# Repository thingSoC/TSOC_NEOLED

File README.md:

# TSOC_NEOLED

**TSOC_NEOLED** is a Eight-Channel WS2812 LED driver expansion board, and can drive
eight (8) to sixteen(16) strips of individually addressable Light Emitting Diodes (LEDs). 

**TSOC_NEOLED** uses a programmable system on chip (PSoC4) with an eight (8) channel driver
to drive hundreds of WS2812 Color LED's, with a default arrangement of 8 (eight strings) of sixty-four(64) LEDs each.

The **TSOC_NEOLED** can provide several different intefaces in order to make
interfacing large numbers of LEDs easy. The default protocol is an I2C interface :

1) I2C Serial DMX-512, Memory Mapped (**TSOC_NEOLED** looks like a 2048 byte I2C SRAM)

Other Interface protocols are possible (Firmware update using FTDI/USB-UART or JTAG) :

- UART Serial DMX-512 (200K Baud, N, 8, 1) with four DMX universes.

- SPI Serial DMX-512, Memory Mapped (**TSOC_NEOLED** looks like a 2048 byte SPI SRAM)

[TSOC_NEOLED](https://github.com/thingSoC/TSOC_NEOLED)

**thingSoC Reference Designs** are example thingSoC implementations that implement
various reference and testing circuits for demonstrating the use of the thingSoC libraries.
These reference designs can serve as starting templates for user designs.

---------------------------------------

## TSOC_NEOLED Application Pictures

Using the TSOC_NEOLED to drive eight(8) strings of color LEDs for lighting our tandem bike for Portland PedalPolooza 2016

[*TSOC_NEOLED*](https://github.com/thingSoC/TSOC_NEOLED)

---------------------------------------

## TSOC_NEOLED Arduino Sketch Examples

Under the "examples" directory are several Arduino IDE examples for using the TSOC_NEOLED board with Arduino IDE.
Using the Arduino "Wire" library for I2C communications, it is simple to control the TSOC_NEOLED

```c
  // Start the Arduino I2C Interface
  wire.begin();

  // Turn the first LED On (i.e. green LED #1) 
  // the LED's are (GRBY) color order in memory
  byte row, column = 0;
  Wire.beginTransmission(TSOC_NEOLED_I2CADDRESS);  // Start the I2C transaction
  Wire.write(row);                                 // Send the high byte of 16 bit memory address
  Wire.write(column);                              // Send the low byte of 16 bit memory address
  Wire.write(TSOC_NEOLED_LED_ON);                  // Send a single data byte  (we could send more...)
  Wire.endTransmission();                          // End the I2C transaction
 
  // Turn the first LED Off (i.e. green LED #1) 
  // the LED's are (GRBY) color order in memory
  Wire.beginTransmission(TSOC_NEOLED_I2CADDRESS);  // Start the I2C transaction
  Wire.write(row);                                 // Send the high byte of 16 bit memory address
  Wire.write(column);                              // Send the low byte of 16 bit memory address
  Wire.write(TSOC_NEOLED_LED_OFF);                  // Send a single data byte  (we could send more...)
  Wire.endTransmission();                          // End the I2C transaction

```

---------------------------------------
## TSOC_NEOLED Programming

You can reprogram the board using any FTDI compatible USB to UART adapter :

[TSOC_NEOLED with FTDI basic](https://github.com/thingSoC/TSOC_NEOLED)

[TSOC_NEOLED with TSOC_USBUART2](https://github.com/thingSoC/TSOC_NEOLED)

[TSOC_NEOLED with TSOC_USBUART2](https://github.com/thingSoC/TSOC_NEOLED)

In order to reprogram the Cypress PSoC4 device, you will need to download and install the PSoC Creator tool, which includes a serial bootloader host application.

Select Tools -> Bootloader Host 

Then select the hex (cyacd) file that you wish to program, and the COM: port of your device. Proess the "Upload" button to reflash teh device.

[PSoC Creator Bootloader Host](https://github.com/thingSoC/TSOC_NEOLED)

---------------------------------------
## Other Applications

The TSOC_NEOLED can also drive other devices, such as Servos, Motors, Realys and more.
This requires custom firmware at the current time.

[TSOC_NEOLED with Servo](https://github.com/thingSoC/TSOC_NEOLED)

---------------------------------------

## TSOC_NEOLED Status <a name="TSOC_NEOLED_status"/>

**04/28/2016:** 
Revision 1.1 - Initial Layout with Eight(8) channel driver.

**06/27/2016:**
Revision 1.2 - Added extra power connections for higher current support.

**07/26/2016:**
Revision 2.0 -

               Moved extra jumpers to the Digital Programming Connector (i.e. boot-mode control).

               Added SAR Bypass capactitors in their place.  
               
               Misc Silkscreen clean up.  
               
               Add Fiducials and DFM cleanup.

---------------------------------------
## TSOC_NEOLED Model Images

[TSOC_NEOLED](https://github.com/thingSoC/TSOC_NEOLED)

[TSOC_NEOLED](https://github.com/thingSoC/TSOC_NEOLED)

---------------------------------------

## TSOC_NEOLED Documentation Index <a name="TSOC_NEOLED_documentation_index"/>

[TSOC_NEOLED Project](http://thingsoc.github.io/projects/TSOC_NEOLED.html)

[TSOC_NEOLED Hardware](https://github.com/thingSoC/TSOC_NEOLED/tree/master/TSOC_NEOLED/hardware)

---------------------------------------

## thingSoC Documentation Index <a name="thingSoC_documentation_index"/>

[thingSoC Organization Website](http://thingSoC.github.io)

[thingSoC FAQ - Frequently Asked Questions](http://thingsoc.github.io/support/faq.html)

---------------------------------------

[ 
*thingSoC*](http://thingsoc.github.io)

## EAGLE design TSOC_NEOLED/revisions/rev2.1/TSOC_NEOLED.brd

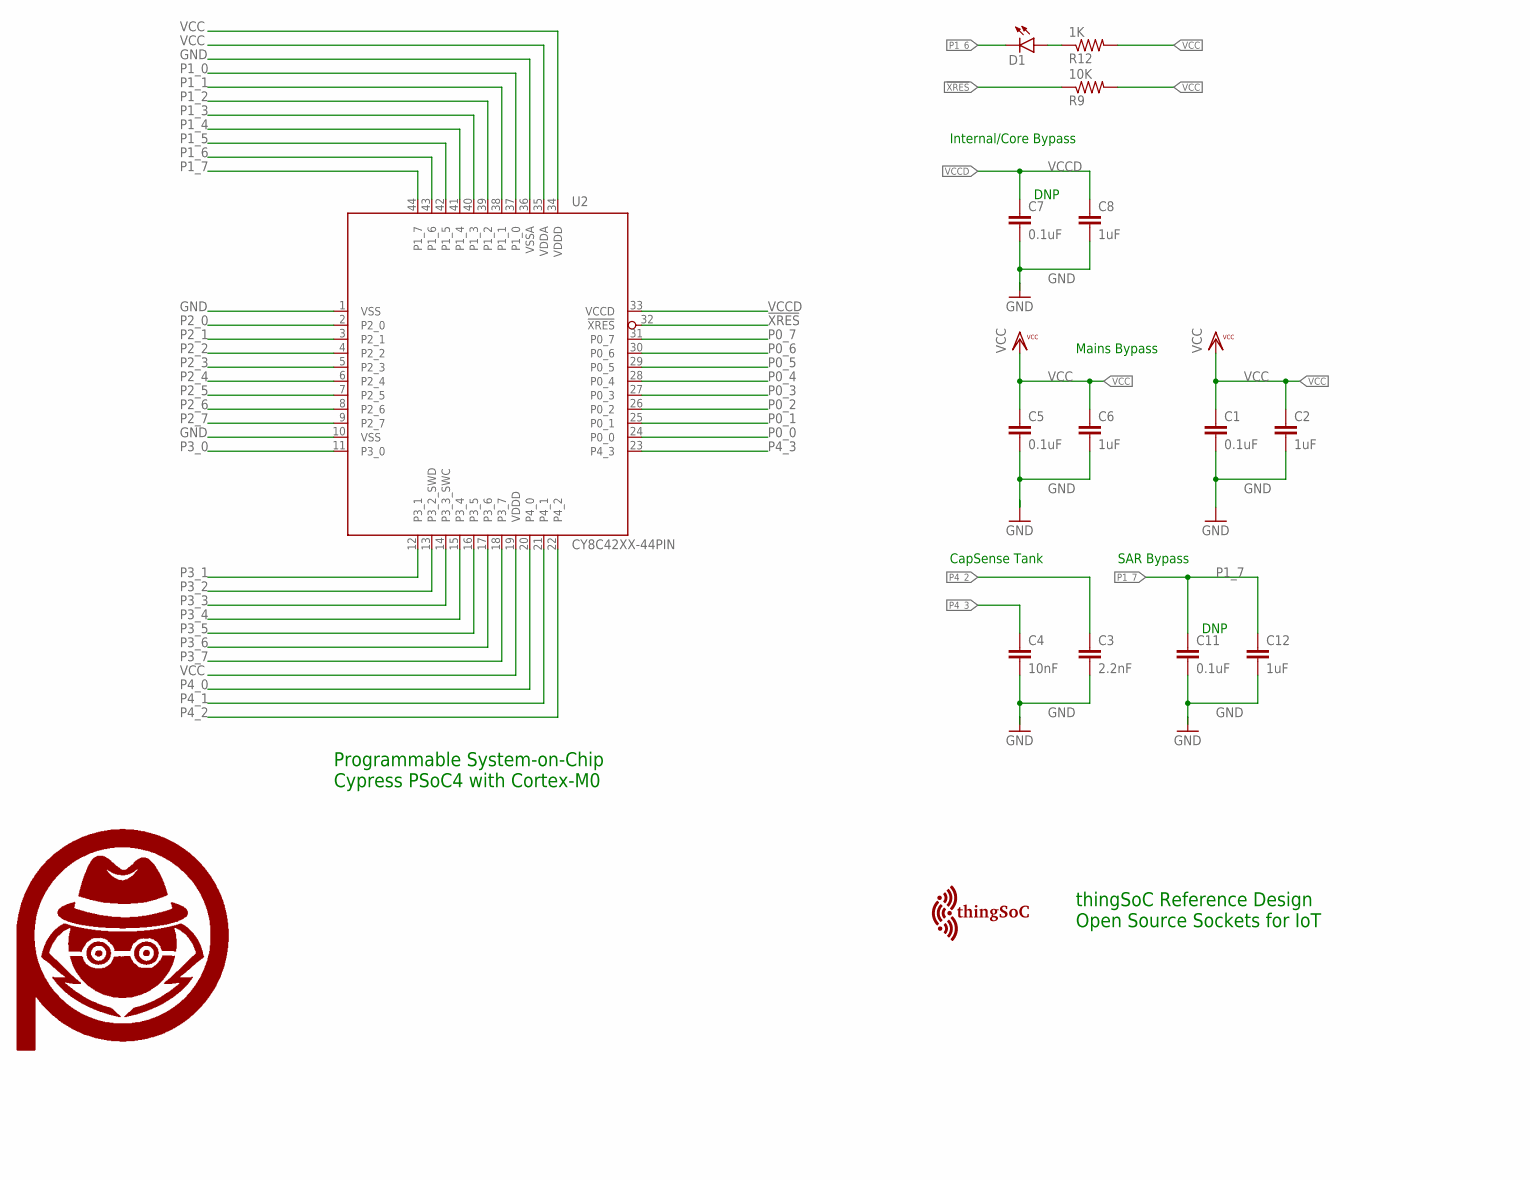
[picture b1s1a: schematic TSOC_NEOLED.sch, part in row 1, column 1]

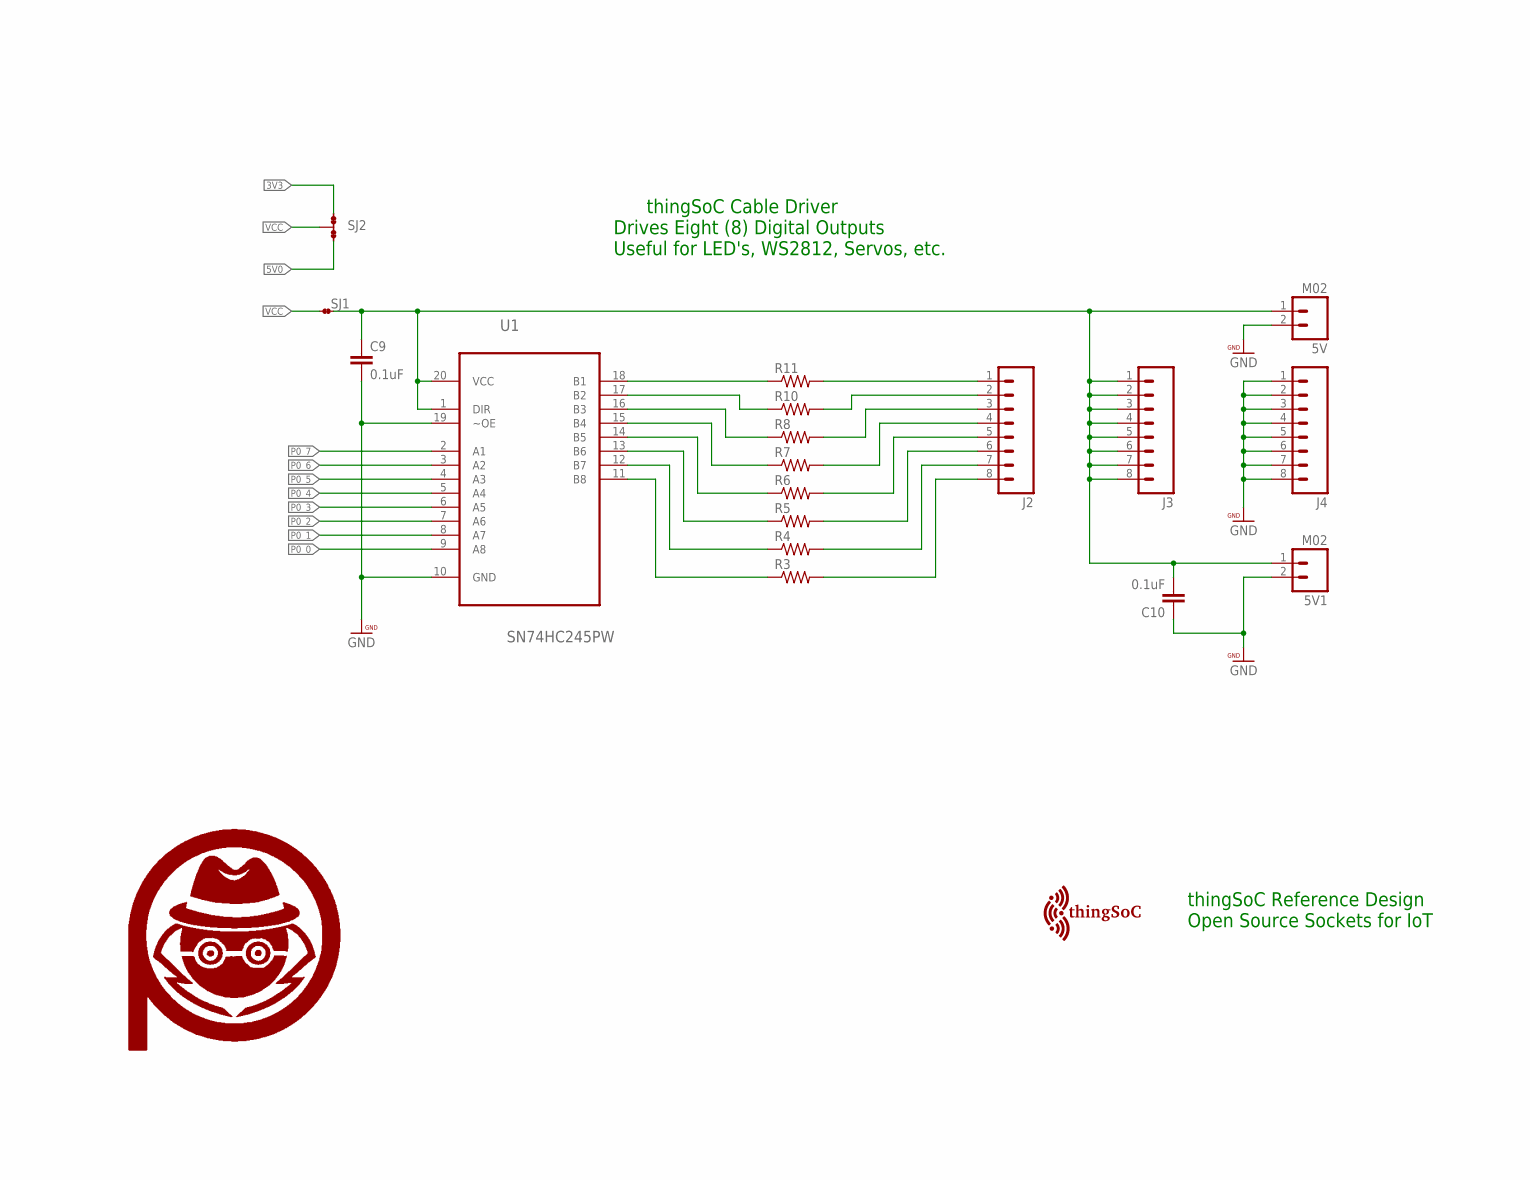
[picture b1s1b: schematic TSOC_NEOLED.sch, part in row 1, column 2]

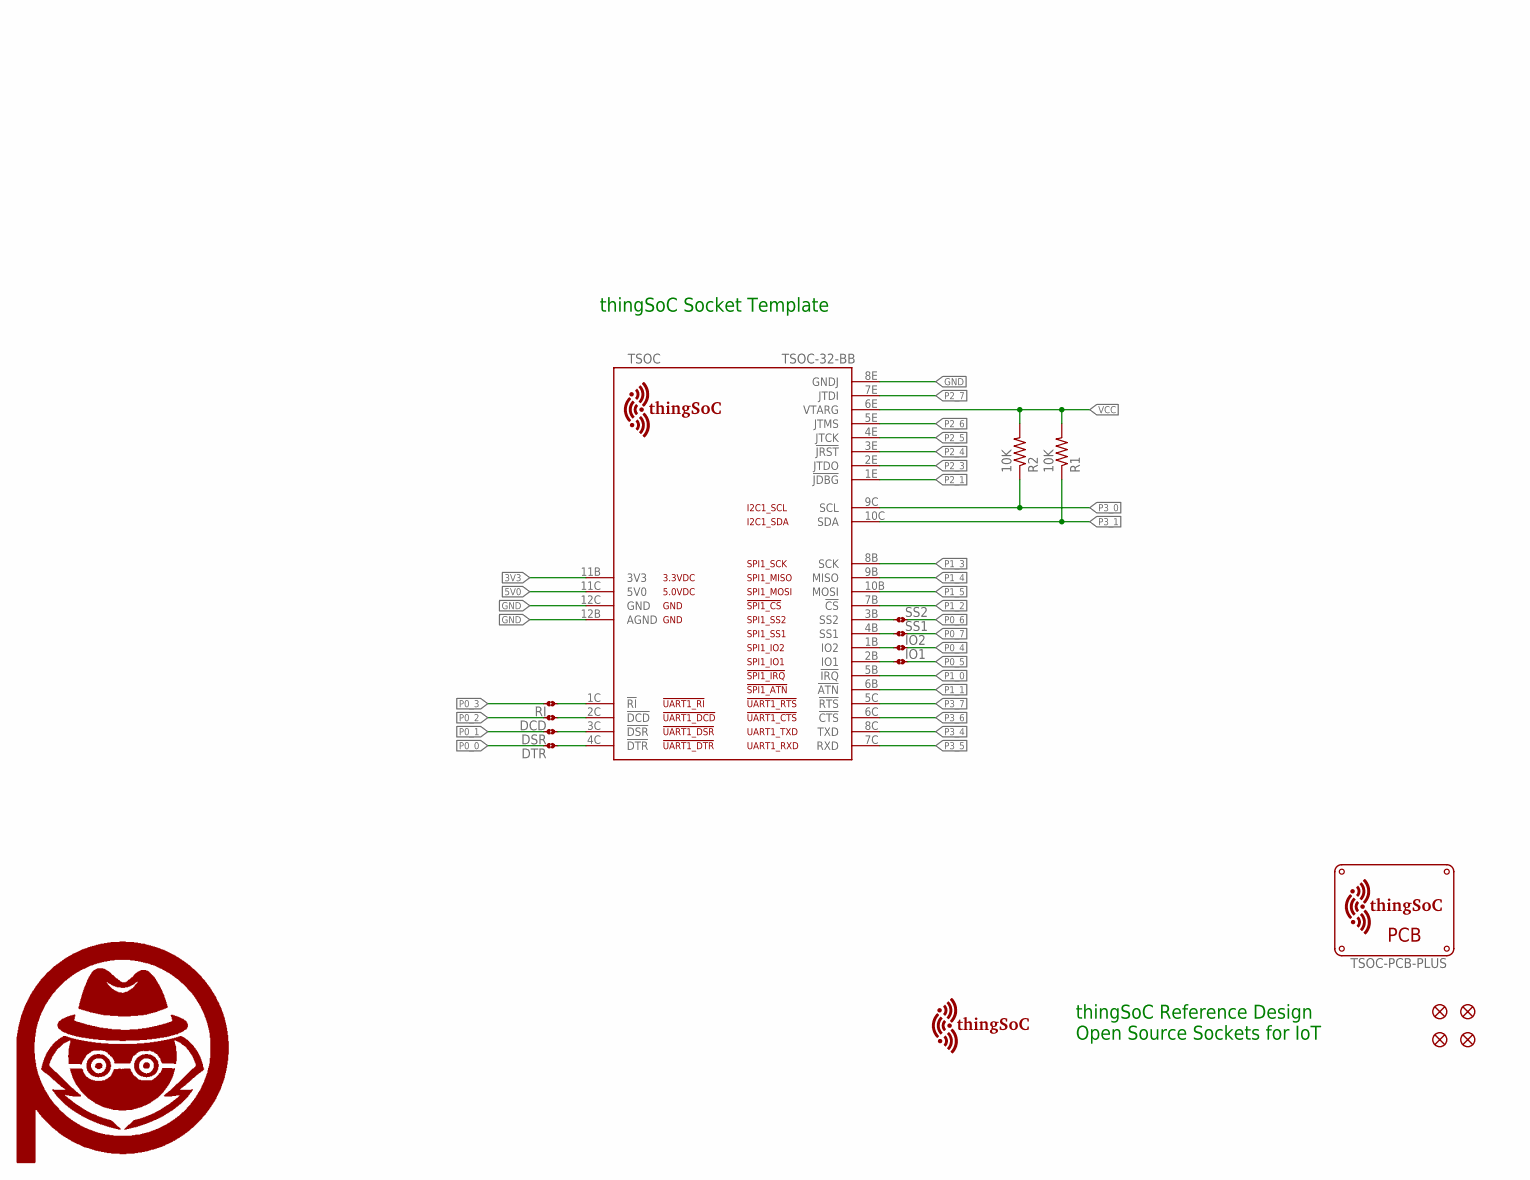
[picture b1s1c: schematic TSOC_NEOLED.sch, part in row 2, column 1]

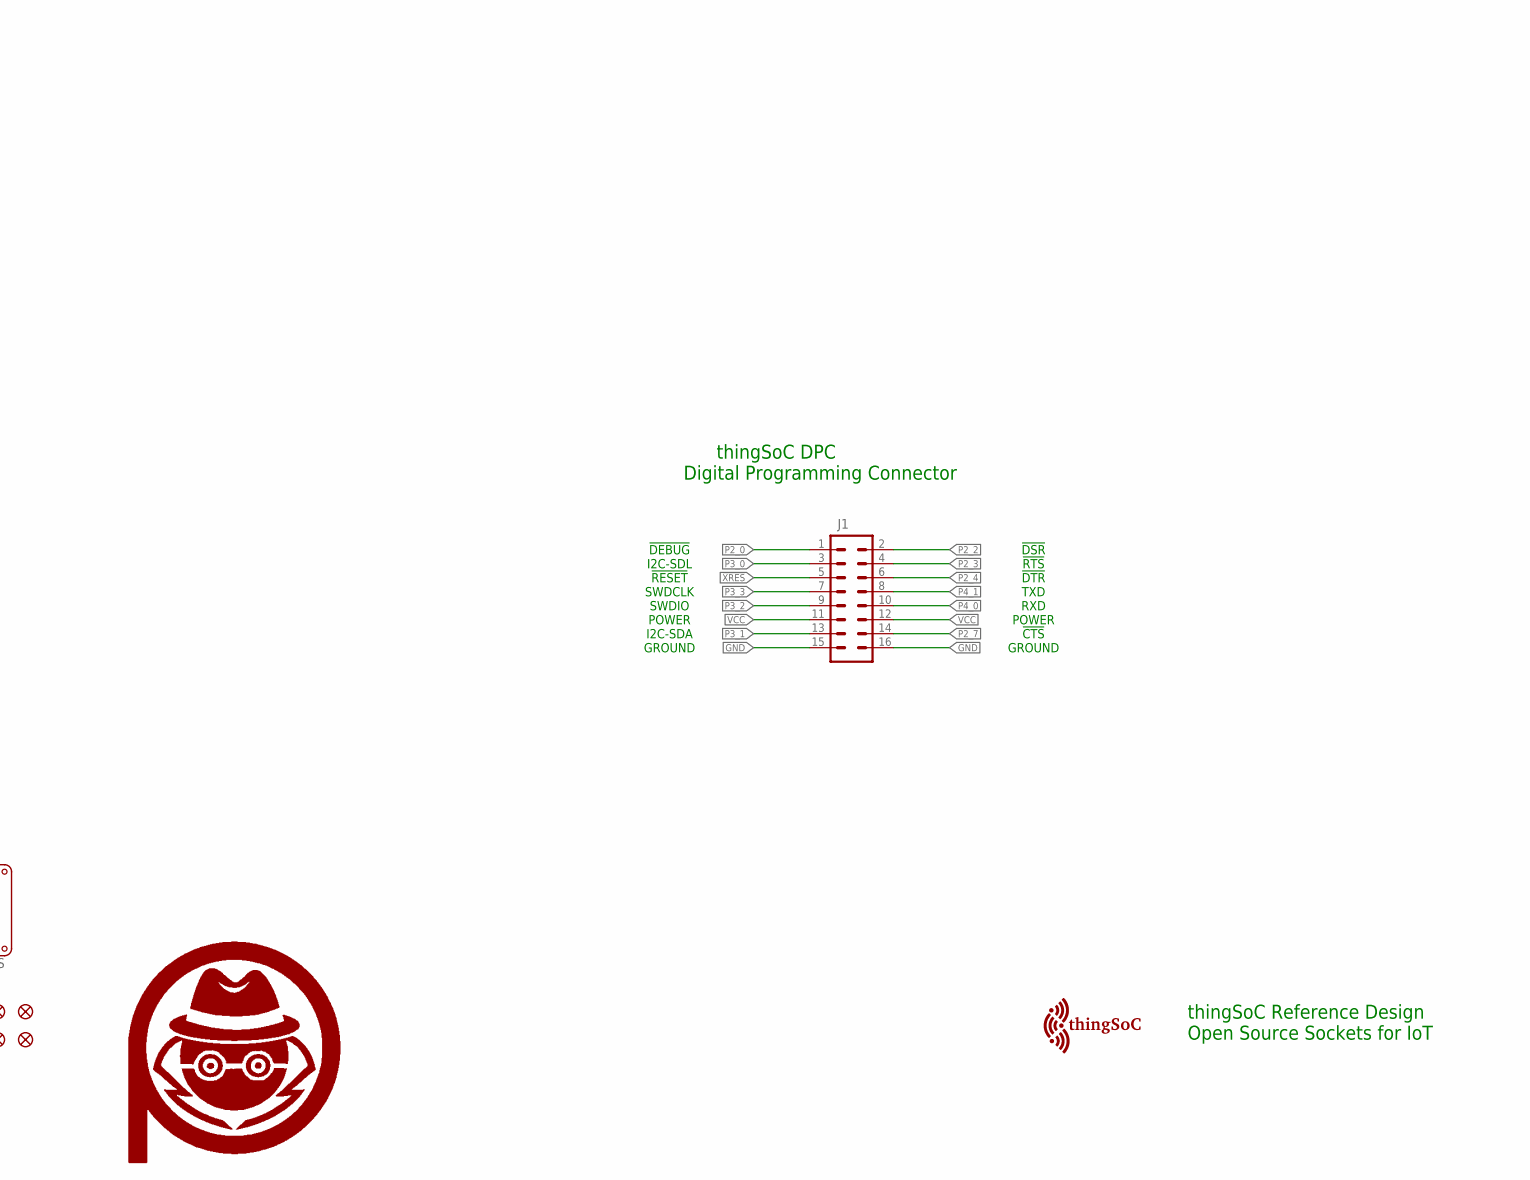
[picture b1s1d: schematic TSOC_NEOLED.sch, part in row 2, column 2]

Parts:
5V, 5V1: M02; 1X02
$$U$1: TSOC-LOGO-SMALL; TSOC-LOGO-SML
$$U$2: TSOC-LOGO-MED
C1, C5, C7, C9, C10, C11: 0.1uF; 0603-CAP
C2, C6, C8, C12: 1uF; 0603-CAP
C3: 2.2nF; 0603-CAP
C4: 10nF; 0603-CAP
D1: LED0603; LED-0603
DCD: JMP-2-NO
DSR: JMP-2-NO
DTR: JMP-2-NO
FID1, FID2, FID3, FID4: FIDUCIALUFIDUCIAL; MICRO-FIDUCIAL
IO1, IO2: JMP-2-NO
J1: M08X2; 2X8
J2, J3, J4: M08; 1X08_ROUND
R1, R2, R9: 10K; 0603-RES
R3, R4, R5, R6, R7, R8, R10, R11: RESISTOR0603-RES; 0603-RES
R12: 1K; 0603-RES
RI: JMP-2-NO
SJ1: JMP-2-NC
SJ2: JMP-3-NC
SS1, SS2: JMP-2-NO
TSOC: TSOC-32-BB; TSOC-BB-S32
U1: SN74HC245PW; SOP65P640X120-20N
U2: CY8C42XX-44PIN; TQFP-10X10-44
U$1: TSOC-PCB-PLUS; TSOC-BB-BRD-PLUS
U$3, U$9, U$10, U$11: PA_LOGO_SYMNULL; NULL_SYM
U$100: TSOC-LOGO-SMALL; TSOC-LOGO-SML
U$101: TSOC-LOGO-LRG

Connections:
3V3: SJ2.1, TSOC.11B (3V3)
5V0: SJ2.3, TSOC.11C (5V0)
!DCD: DCD.1, TSOC.2C (!DCD)
!DSR: DSR.1, TSOC.3C (!DSR)
!DTR: DTR.1, TSOC.4C (!DTR)
!R!: RI.1, TSOC.1C (!RI)
!XRES: J1.5, R9.1, U2.32 (!XRES)
GND: 5V.2, 5V1.2, C1.2, C2.2, C3.2, C4.2, C5.2, C6.2, C7.2, C8.2, C9.2, C10.1, C11.2, C12.2, J1.15, J1.16, J4.1, J4.2, J4.3, J4.4, J4.5, J4.6, J4.7, J4.8, TSOC.8E (GNDJ), TSOC.12B (AGND), TSOC.12C (GND), U1.10 (GND), U1.19 (~OE), U2.1 (VSS), U2.10 (VSS), U2.36 (VSSA)
IO1: IO1.1, TSOC.2B (IO1)
IO2: IO2.1, TSOC.1B (IO2)
unnamed: J2.1, R11.2
unnamed: J2.2, R10.2
unnamed: J2.3, R8.2
unnamed: J2.4, R7.2
unnamed: J2.5, R6.2
unnamed: J2.6, R5.2
unnamed: J2.7, R4.2
unnamed: J2.8, R3.2
unnamed: R11.1, U1.18 (B1)
unnamed: R10.1, U1.17 (B2)
unnamed: R8.1, U1.16 (B3)
unnamed: R7.1, U1.15 (B4)
unnamed: R6.1, U1.14 (B5)
unnamed: R5.1, U1.13 (B6)
unnamed: R4.1, U1.12 (B7)
unnamed: R3.1, U1.11 (B8)
unnamed: D1.A, R12.1
P0_0: DTR.2, U1.9 (A8), U2.24 (P0_0)
P0_1: DSR.2, U1.8 (A7), U2.25 (P0_1)
P0_2: DCD.2, U1.7 (A6), U2.26 (P0_2)
P0_3: RI.2, U1.6 (A5), U2.27 (P0_3)
P0_4: IO2.2, U1.5 (A4), U2.28 (P0_4)
P0_5: IO1.2, U1.4 (A3), U2.29 (P0_5)
P0_6: SS2.2, U1.3 (A2), U2.30 (P0_6)
P0_7: SS1.2, U1.2 (A1), U2.31 (P0_7)
P1_0: TSOC.5B (!IRQ), U2.37 (P1_0)
P1_1: TSOC.6B (!ATN), U2.38 (P1_1)
P1_2: TSOC.7B (!CS), U2.39 (P1_2)
P1_3: TSOC.8B (SCK), U2.40 (P1_3)
P1_4: TSOC.9B (MISO), U2.41 (P1_4)
P1_5: TSOC.10B (MOSI), U2.42 (P1_5)
P1_6: D1.C, U2.43 (P1_6)
P1_7: C11.1, C12.1, U2.44 (P1_7)
P2_0: J1.1, U2.2 (P2_0)
P2_1: TSOC.1E (!JDBG), U2.3 (P2_1)
P2_2: J1.2, U2.4 (P2_2)
P2_3: J1.4, TSOC.2E (JTDO), U2.5 (P2_3)
P2_4: J1.6, TSOC.3E (!JRST), U2.6 (P2_4)
P2_5: TSOC.4E (JTCK), U2.7 (P2_5)
P2_6: TSOC.5E (JTMS), U2.8 (P2_6)
P2_7: J1.14, TSOC.7E (JTDI), U2.9 (P2_7)
P3_0: J1.3, R2.1, TSOC.9C (SCL), U2.11 (P3_0)
P3_1: J1.13, R1.1, TSOC.10C (SDA), U2.12 (P3_1)
P3_2: J1.9, U2.13 (P3_2_SWD)
P3_3: J1.7, U2.14 (P3_3_SWC)
P3_4: TSOC.8C (TXD), U2.15 (P3_4)
P3_5: TSOC.7C (RXD), U2.16 (P3_5)
P3_6: TSOC.6C (!CTS), U2.17 (P3_6)
P3_7: TSOC.5C (!RTS), U2.18 (P3_7)
P4_0: J1.10, U2.20 (P4_0)
P4_1: J1.8, U2.21 (P4_1)
P4_2: C3.1, U2.22 (P4_2)
P4_3: C4.1, U2.23 (P4_3)
SS1: SS1.1, TSOC.4B (SS1)
SS2: SS2.1, TSOC.3B (SS2)
VCC: C1.1, C2.1, C5.1, C6.1, J1.11, J1.12, R1.2, R2.2, R9.2, R12.2, SJ1.1, SJ2.2, TSOC.6E (VTARG), U2.19 (VDDD), U2.34 (VDDD), U2.35 (VDDA)
VCCD: C7.1, C8.1, U2.33 (VCCD)
VEXT: 5V.1, 5V1.1, C9.1, C10.2, J3.1, J3.2, J3.3, J3.4, J3.5, J3.6, J3.7, J3.8, SJ1.2, U1.1 (DIR), U1.20 (VCC)

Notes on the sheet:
DNP
Internal/Core Bypass
Mains Bypass
I2C-SDA
I2C-SDL
!RESET
SWDCLK
SWDIO
POWER
GROUND
!DEBUG
!DSR
!RTS
!CTS
!DTR
TXD
RXD
CapSense Tank
thingSoC Reference Design Open Source Sockets for IoT
SAR Bypass
thingSoC DPC Digital Programming Connector
thingSoC Cable Driver Drives Eight (8) Digital Outputs Useful for LED's, WS2812, Servos, etc.
thingSoC Socket Template
Programmable System-on-Chip Cypress PSoC4 with Cortex-M0

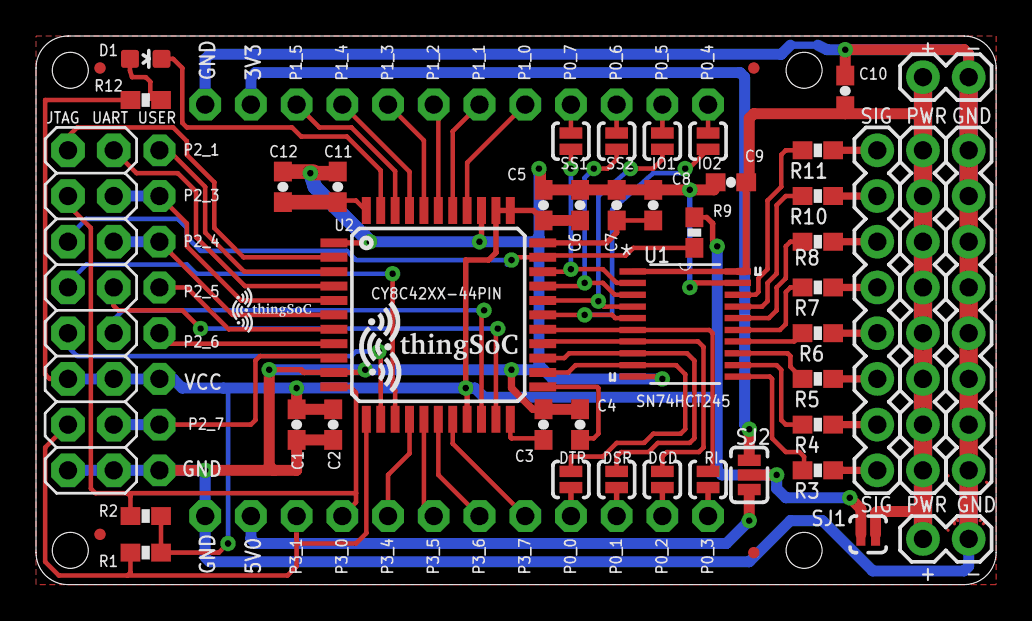
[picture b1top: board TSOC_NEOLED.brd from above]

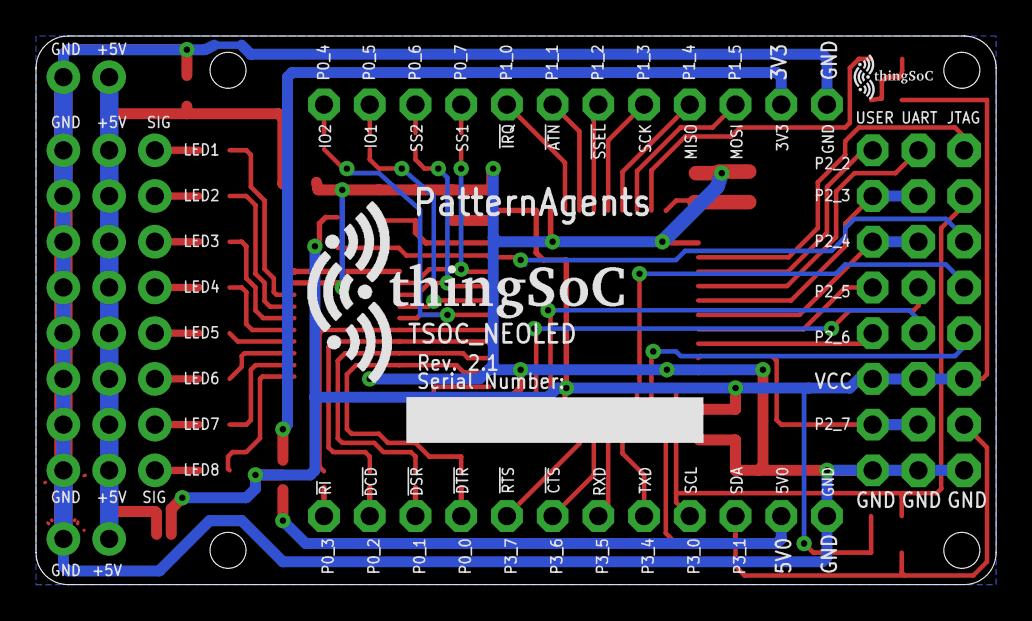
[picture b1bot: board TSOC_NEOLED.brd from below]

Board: 2 copper layers, 53.3 x 30.5 mm, 57 parts (2 on the bottom side), 68 nets.

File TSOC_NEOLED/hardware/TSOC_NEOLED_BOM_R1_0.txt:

Partlist exported from /home/moxon/github/TSOC_NEOLED/TSOC_NEOLED/TSOC_NEOLED.sch at 4/29/16 10:46 AM

Qty Value           Device               Package           Parts                                 Description                                                     
8                   JMP-2-NO             JMP-2-NO          DCD, DSR, DTR, IO1, IO2, RI, SS1, SS2 Two Terminal Jumper - Normally Open                             
1                   LED0603              LED-0603          D1                                    LEDs                                                            
3                   M08                  1X08_ROUND        J2, J3, J4                            Header 8                                                        
1                   M08X2                2X8               J1                                    .1" headers, two rows of 8 each                                 
8                   RESISTOR0603-RES     0603-RES          R3, R4, R5, R6, R7, R8, R10, R11      Resistor                                                        
4   0.1uF           CAP0603-CAP          0603-CAP          C1, C5, C7, C9                        Capacitor                                                       
1   10K             RESISTOR_SFE0603-RES 0603-RES          R9                                    Resistor                                                        
1   10nF            CAP0603-CAP          0603-CAP          C4                                    Capacitor                                                       
1   1K              RESISTOR_SFE0603-RES 0603-RES          R12                                   Resistor                                                        
3   1uF             CAP0603-CAP          0603-CAP          C2, C6, C8                            Capacitor                                                       
1   2.2nF           CAP0603-CAP          0603-CAP          C3                                    Capacitor                                                       
2   2K2             RESISTOR_SFE0603-RES 0603-RES          R1, R2                                Resistor                                                        
1   CY8C42XX-44PIN  CY8C42XX-44PIN       TQFP-10X10-44     U2                                    Cypress PSoC® 4 - Programmable System on Chip,  Cortex-M0 Based 
3   JMP-3-1_2       JMP-3-1_2            JMP-3-1_2         SJ1, SJ2, SJ3                         Three Terminal Jumper - 1 & 2 Connected                         
3   M02             M02                  1X02              5V, SP1, SP2                                                                                          
1   SN74HC245PW     SN74HC245PW          SOP65P640X120-20N U1                                    OCTAL BUS TRANSCEIVERS                                          
1   TSOC-32-BB      TSOC-32-BB           TSOC-BB-S32       TSOC                                  thingSoC Thirty-Two (32) Pin Socket                             
1   TSOC-LOGO-LRG   TSOC-LOGO-LRG        TSOC-LOGO-LRG     U$101                                 thingSoC Logo                                                   
1   TSOC-LOGO-MED   TSOC-LOGO-MED        TSOC-LOGO-MED     $$U$2                                 thingSoC Logo                                                   
2   TSOC-LOGO-SMALL TSOC-LOGO-SMALL      TSOC-LOGO-SML     $$U$1, U$100                          thingSoC Logo                                                   
1   TSOC-PCB-PLUS   TSOC-PCB-PLUS        TSOC-BB-BRD-PLUS  U$3                                   thingSoC PCB Outlines

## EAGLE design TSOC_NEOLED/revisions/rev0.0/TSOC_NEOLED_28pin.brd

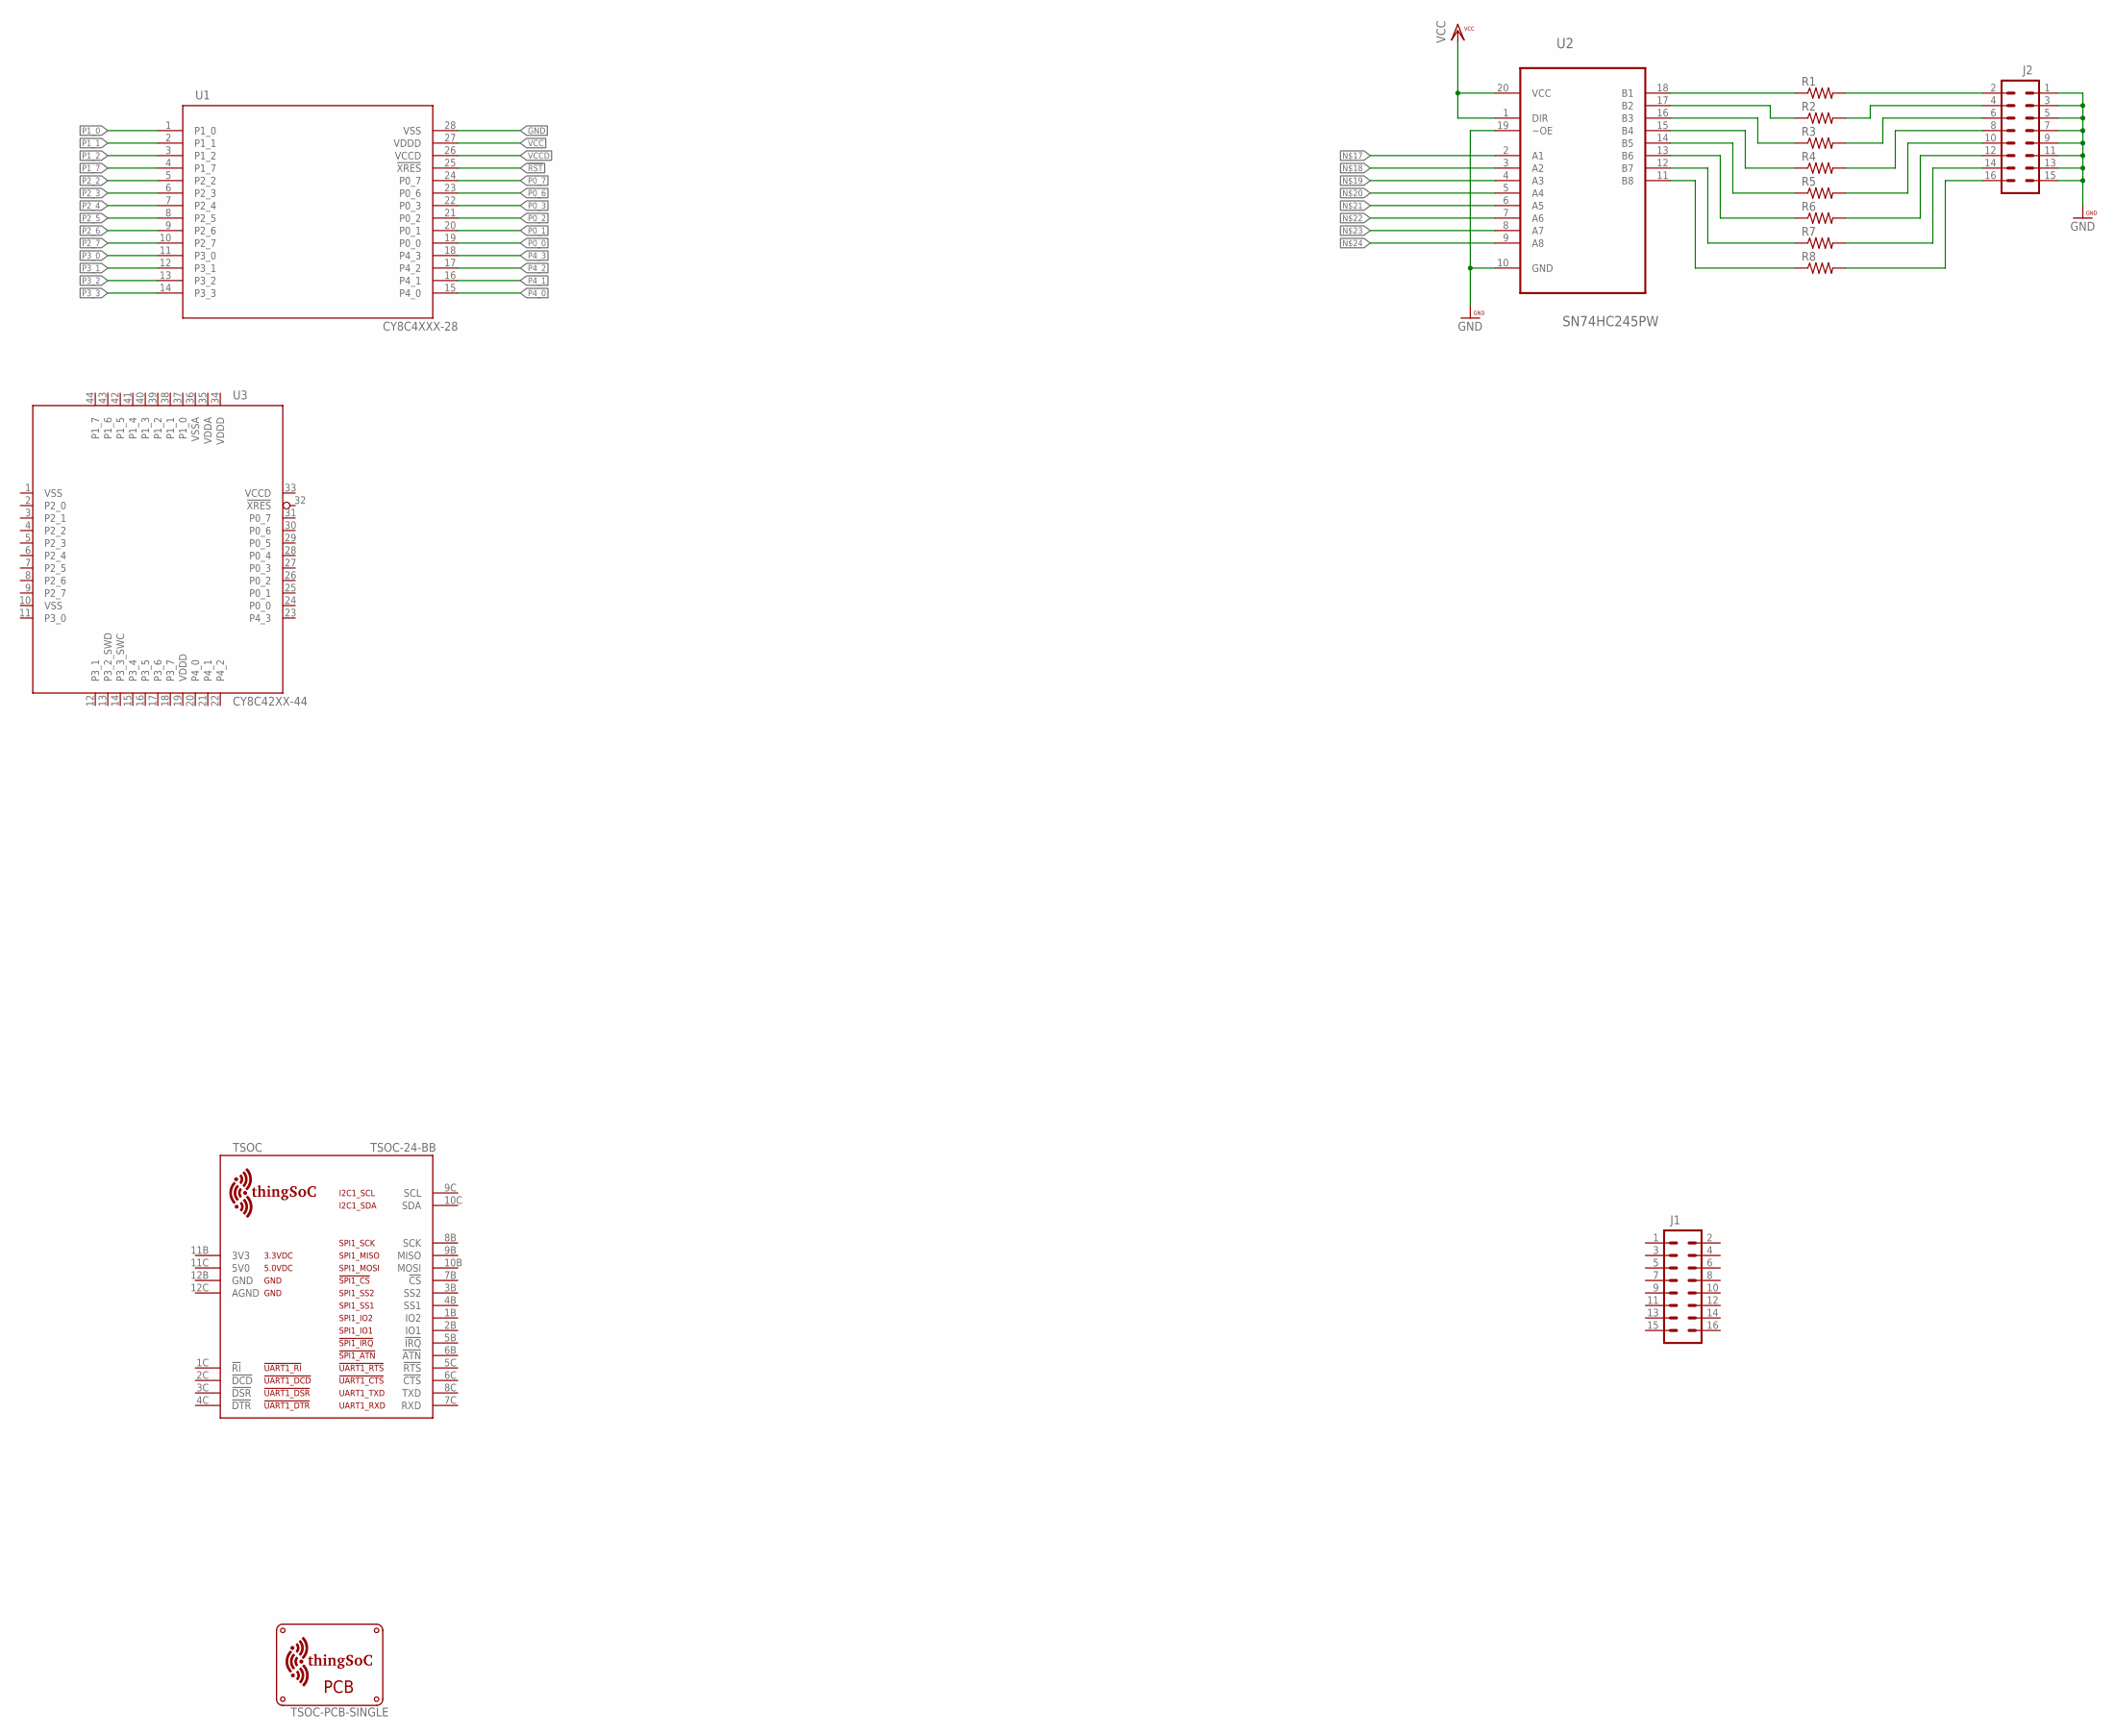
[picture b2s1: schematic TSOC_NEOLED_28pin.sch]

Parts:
J1, J2: M08X2; 2X8
R1, R2, R3, R4, R5, R6, R7, R8: RESISTOR0603-RES; 0603-RES
TSOC: TSOC-24-BB; TSOC-BB-S24
U1: CY8C4XXX-28; SSOP28
U2: SN74HC245PW; SOP65P640X120-20N
U3: CY8C42XX-44; TQFP-10X10-44
U$3: TSOC-PCB-SINGLE; TSOC-BB-BRD

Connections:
!RST: U1.25 (!XRES)
GND: J2.1, J2.3, J2.5, J2.7, J2.9, J2.11, J2.13, J2.15, U1.28 (VSS), U2.10 (GND), U2.19 (~OE)
unnamed: J2.2, R1.2
unnamed: J2.4, R2.2
unnamed: J2.6, R3.2
unnamed: J2.8, R4.2
unnamed: J2.10, R5.2
unnamed: J2.12, R6.2
unnamed: J2.14, R7.2
unnamed: J2.16, R8.2
unnamed: R1.1, U2.18 (B1)
unnamed: R2.1, U2.17 (B2)
unnamed: R3.1, U2.16 (B3)
unnamed: R4.1, U2.15 (B4)
unnamed: R5.1, U2.14 (B5)
unnamed: R6.1, U2.13 (B6)
unnamed: R7.1, U2.12 (B7)
unnamed: R8.1, U2.11 (B8)
P0_0: U1.19 (P0_0)
P0_1: U1.20 (P0_1)
P0_2: U1.21 (P0_2)
P0_3: U1.22 (P0_3)
P0_6: U1.23 (P0_6), U3.30 (P0_6)
P0_7: U1.24 (P0_7)
P1_0: U1.1 (P1_0)
P1_1: U1.2 (P1_1)
P1_2: U1.3 (P1_2), U3.39 (P1_2)
P1_7: U1.4 (P1_7)
P2_2: U1.5 (P2_2), U3.4 (P2_2)
P2_3: U1.6 (P2_3)
P2_4: U1.7 (P2_4)
P2_5: U1.8 (P2_5)
P2_6: U1.9 (P2_6), U3.8 (P2_6)
P2_7: U1.10 (P2_7)
P3_0: U1.11 (P3_0)
P3_1: U1.12 (P3_1)
P3_2: U1.13 (P3_2)
P3_3: U1.14 (P3_3)
P3_6: U3.17 (P3_6)
P4_0: U1.15 (P4_0)
P4_1: U1.16 (P4_1)
P4_2: U1.17 (P4_2)
P4_3: U1.18 (P4_3)
VCC: U1.27 (VDDD), U2.1 (DIR), U2.20 (VCC)
VCCD: U1.26 (VCCD)

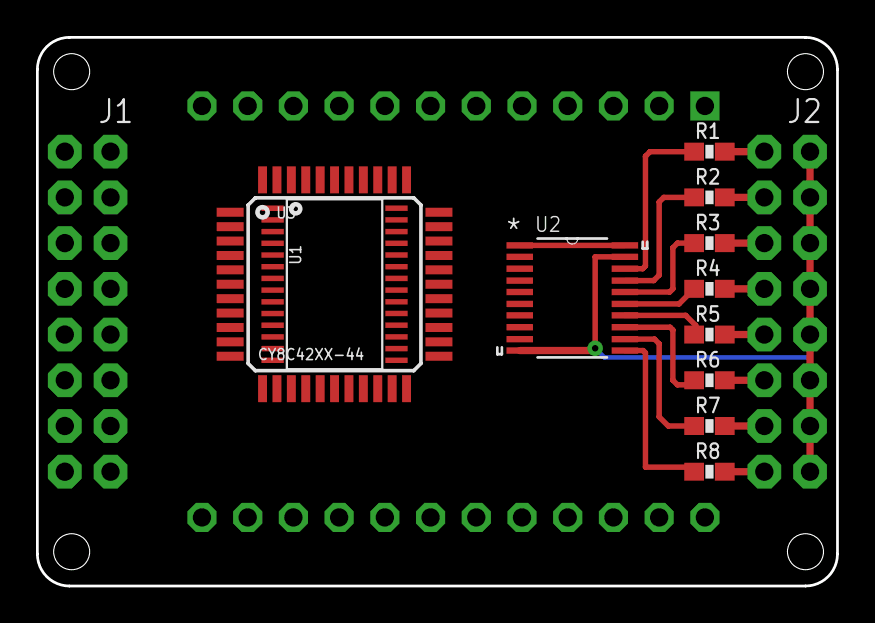
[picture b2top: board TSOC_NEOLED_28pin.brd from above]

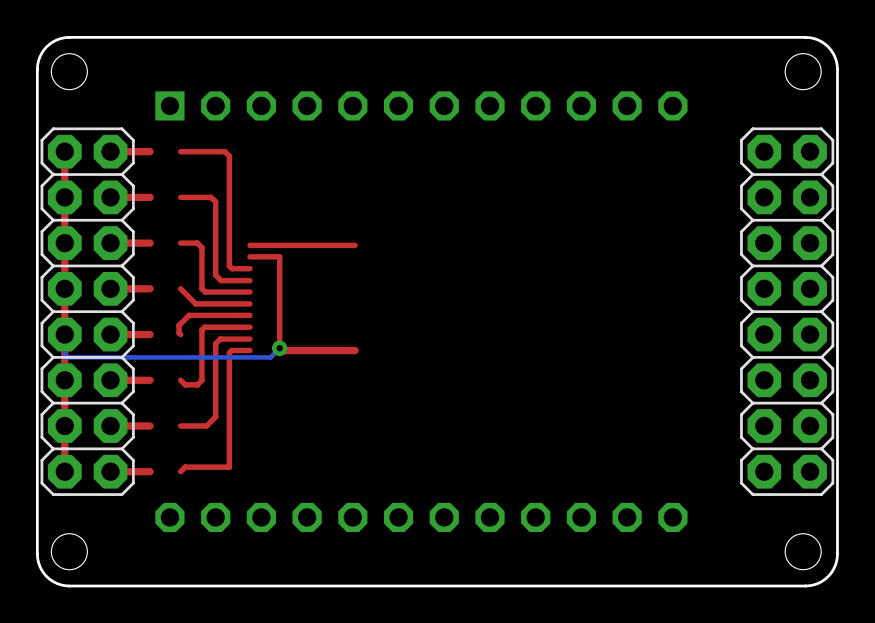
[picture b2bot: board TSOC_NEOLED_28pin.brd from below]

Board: 2 copper layers, 44.5 x 30.5 mm, 15 parts (2 on the bottom side), 22 nets.

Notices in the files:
parts and their libraries:
PatternAgents-Beautify: License : http://creativecommons.org/licenses/by-sa/3.0
(Creative Commons 3.0)
thingSoC: License : http://creativecommons.org/licenses/by-sa/4.0
(Creative Commons 4.0)
